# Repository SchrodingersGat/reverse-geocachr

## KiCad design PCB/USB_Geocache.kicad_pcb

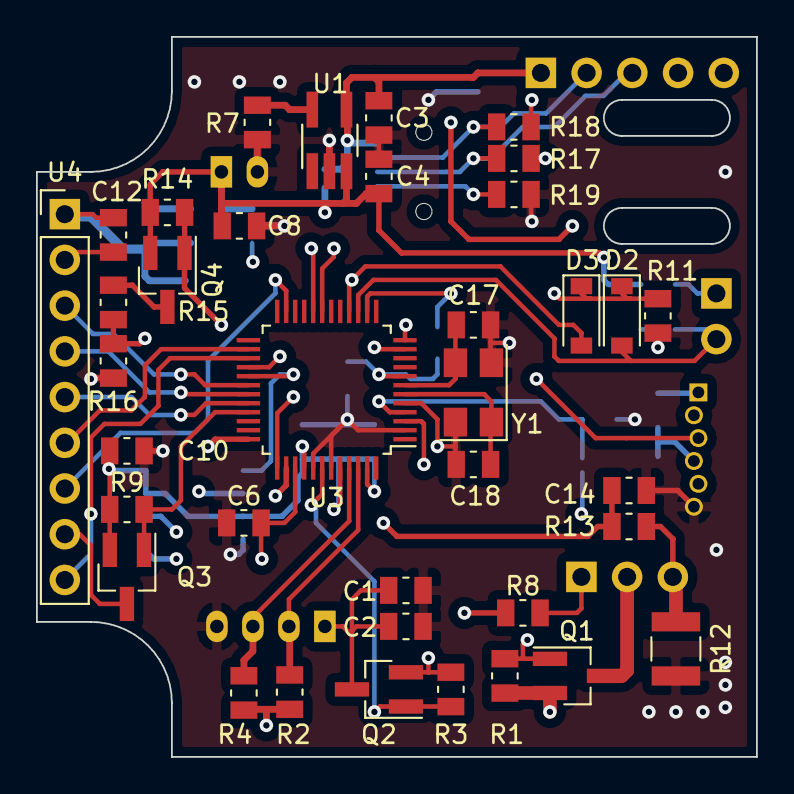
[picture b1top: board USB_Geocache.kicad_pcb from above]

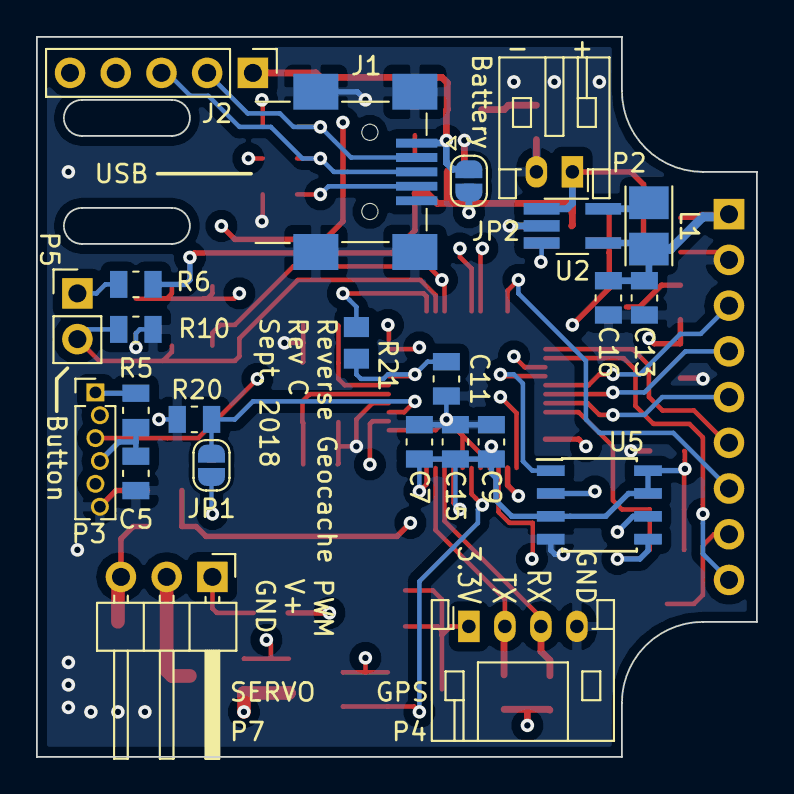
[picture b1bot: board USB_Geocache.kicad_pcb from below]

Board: 4 copper layers, 40.0 x 40.0 mm, 61 parts (24 on the bottom side), 39 nets.

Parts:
C1, C5, C7, C8, C9, C10, C11, C15, C16: 0.1uF; C_0805_2012Metric
C2, C6, C12, C13, C14: 10uF; C_0805_2012Metric
C3, C4: 4.7uF; C_0805_2012Metric
C17, C18: 18pF; C_0805_2012Metric
D2, D3: D; D_SOD-123
J1: USB_B_Mini; USB_Mini-B_Lumber_2486_Horizontal
J2: USB_ALT; PinHeader_1x05_P2.54mm_Vertical
JP1: Boot; SolderJumper-2_P1.3mm_Open_RoundedPad1.0x1.5mm
JP2: 5V; SolderJumper-2_P1.3mm_Open_RoundedPad1.0x1.5mm
L1: 10uH; L_Taiyo-Yuden_NR-24xx_HandSoldering
P2: Battery; JST_PH_S2B-PH-K_1x02_P2.00mm_Horizontal
P3: SWD; PinHeader_1x06_P1.27mm_Vertical
P4: GPS; JST_PH_S4B-PH-K_1x04_P2.00mm_Horizontal
P5: Button; PinHeader_1x02_P2.54mm_Vertical
P7: Servo; PinHeader_1x03_P2.54mm_Horizontal
Q1, Q2, Q3, Q4: DMP3099L; SOT-23_Handsoldering
R1, R3, R5, R6, R7, R8, R9, R11, R13, R14, R15: 4K7; R_0805_2012Metric
R2, R4, R10, R16, R20, R21: 10K; R_0805_2012Metric
R12: 0R1; R_1210_3225Metric
R17, R18: 0; R_0805_2012Metric
R19: 100K; R_0805_2012Metric
U1: MCP73831-2-OT; TSOT-23-5_HandSoldering
U2: LM3670MF; TSOT-23-5_HandSoldering
U3: LPC11U68JBD48E; LQFP-48_7x7mm_P0.5mm
U4: CR2013-MI2120; PinHeader_1x09_P2.54mm_Vertical
U5: 25LC640A-I/SN; SOIC-8_3.9x4.9mm_P1.27mm
Y1: 8MHz; Crystal_SMD_5032-4Pin_5.0x3.2mm

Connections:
+3V3: C7.1, C9.1, C10.2, C11.1, C12.1, C13.1, C15.1, C16.1, JP1.1, L1.1, P3.1, Q2.2, Q3.2, R2.1, R3.1, R4.1, R5.1, R8.1, R9.1, R21.1, U2.4, U3.8, U3.40, U3.44, U3.47, U4.1, U5.3, U5.7, U5.8
+5V: C3.1, J1.1, J2.1, JP2.1, U1.4
+BATT: C4.1, C8.1, JP2.2, P2.1, Q1.2, Q4.2, R1.2, R6.1, R14.1, U1.3, U2.1
/BUTTON: D2.2, P5.2, R10.1, U3.15
/CS_EEPROM: U3.29, U5.1
/EN: D2.1, D3.1, R11.1, U2.3
/GPS_PWR: Q2.1, R3.2, U3.42
/GPS_RX: P4.3, R4.2, U3.45
/GPS_TX: P4.2, R2.2, U3.46
/I_SERVO: C14.1, R13.1, U3.38
/LDC_BL: Q3.1, R9.2, U3.33
/OSC1: C18.1, U3.6, Y1.1
/OSC2: C17.1, U3.7, Y1.3
/SERVO_EN: Q1.1, R1.1, U3.11
/SERVO_PWM: P7.1, R8.2, U3.12
/SPI_MISO: U3.27, U4.9, U5.2
/SPI_MOSI: U3.26, U4.6, U5.5
/SPI_SCK: U3.23, U4.7, U5.6
/SWCLK: P3.3, U3.28
/SWDIO: P3.2, U3.37
/SW_ENABLE: D3.2, U3.16
/SW_RESET: C5.1, P3.4, R5.2, U3.3
/USB_D+: R17.1, U3.20
/USB_D-: R18.1, U3.19
/VMEAS_CTRL: Q4.1, R14.2, U3.36
/V_BATT: C6.1, R15.2, R16.1, U3.39
GND: C1.2, C2.2, C3.2, C4.2, C5.2, C6.2, C7.2, C8.2, C9.2, C10.1, C11.2, C12.2, C13.2, C14.2, C15.2, C16.2, C17.2, C18.2, J1.5, J1.6, J2.5, P2.2, P3.6, P4.4, R7.2, R10.2, R11.2, R12.2, R16.2, R19.2, R20.2, U1.2, U2.2, U3.2, U3.5, U3.41, U3.43, U4.2, U5.4, Y1.2, Y1.4
unnamed: C1.1, C2.1, P4.1, Q2.3
unnamed: J1.2, J2.2, R18.2
unnamed: J1.3, J2.3, R17.2
unnamed: J1.4, J2.4, R19.1
unnamed: JP1.2, R20.1, U3.4
unnamed: L1.2, U2.5
unnamed: P5.1, R6.2
unnamed: P7.2, Q1.3
unnamed: P7.3, R12.1, R13.2
unnamed: Q4.3, R15.1
unnamed: R7.1, U1.5
unnamed: R21.2, U3.14

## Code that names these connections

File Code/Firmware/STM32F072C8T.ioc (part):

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Mcu.Name=STM32F072C(8-B)Tx
Mcu.Package=LQFP48
Mcu.UserName=STM32F072C8Tx
PA0.GPIOParameters=GPIO_Label
PA0.GPIO_Label=V_BAT
PA0.Mode=IN0
PA0.Signal=ADC_IN0
PA1.GPIOParameters=GPIO_Label
PA1.GPIO_Label=I_SERVO
PA1.Mode=IN1
PA1.Signal=ADC_IN1
PA11.Mode=Device
PA11.Signal=USB_DM
PA12.Mode=Device
PA12.Signal=USB_DP
PA13.Mode=Serial_Wire
PA13.Signal=SYS_SWDIO
PA14.Mode=Serial_Wire
PA14.Signal=SYS_SWCLK
PA2.GPIOParameters=GPIO_Label
PA2.GPIO_Label=GPS_TX
PA2.Mode=Asynchronous
PA2.Signal=USART2_TX
PA3.GPIOParameters=GPIO_Label
PA3.GPIO_Label=GPS_RX
PA3.Mode=Asynchronous
PA3.Signal=USART2_RX
PA4.GPIOParameters=GPIO_Label
PA4.GPIO_Label=GPS_PWR
PA4.Signal=GPIO_Output
PA5.Mode=Full_Duplex_Master
PA5.Signal=SPI1_SCK
PA6.Mode=Full_Duplex_Master
PA6.Signal=SPI1_MISO
PA7.Mode=Full_Duplex_Master
PA7.Signal=SPI1_MOSI
PA8.GPIOParameters=GPIO_Label
PA8.GPIO_Label=SERVO_PWM
PA8.Signal=GPIO_Output
PA9.GPIOParameters=GPIO_Label
PA9.GPIO_Label=SERVO_PWR
PA9.Signal=GPIO_Output
PB0.GPIOParameters=GPIO_Label
PB0.GPIO_Label=LCD_CS
PB0.Signal=GPIO_Output
PB1.GPIOParameters=GPIO_Label
PB1.GPIO_Label=LCD_DC
PB1.Signal=GPIO_Output
PB10.GPIOParameters=GPIO_Label
PB10.GPIO_Label=LCD_RESET
PB10.Signal=GPIO_Output
PB2.GPIOParameters=GPIO_Label
PB2.GPIO_Label=LCD_BL
PB2.Signal=GPIO_Output
PB5.GPIOParameters=GPIO_Label
PB5.GPIO_Label=CS_EEPROM
PB5.Signal=GPIO_Output
PB8.GPIOParameters=GPIO_Label
PB8.GPIO_Label=BUTTON
PB8.Signal=GPIO_Input
PB9.GPIOParameters=GPIO_Label
PB9.GPIO_Label=SW_ENABLE
PB9.Signal=GPIO_Output
RCC.SYSCLKFreq_VALUE=36000000
RCC.SYSCLKSource=RCC_SYSCLKSOURCE_PLLCLK

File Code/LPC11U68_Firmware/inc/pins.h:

#ifndef INC_PINS_H_
#define INC_PINS_H_

#include <stdint.h>
#include <stdbool.h>

#include "board.h"

/* GPIO Pins (General)
 * SW_ENABLE = P0.5
 * BUTTON = P0.4
 * SERVO_PWM = P2.2 (STC0_OUT1)
 * SERVO_EN = P0.2
 * GPS_PWR = P0.17
 */

#define ENABLE_PORT 1
#define ENABLE_PIN 20

#define BUTTON_PORT 0
#define BUTTON_PIN 4

#define SERVO_PWM_PORT 2
#define SERVO_PWM_PIN 2

#define SERVO_EN_PORT 0
#define SERVO_EN_PIN 2

#define GPS_PWR_PORT 0
#define GPS_PWR_PIN 17

/* LCD GPIO Pins as follows:
 * CS = P0.11		- Chip Select
 * DC = P0.12		- Data / Command
 * RESET = P0.13	- Reset
 * BL = P0.14		- Backlight enable
 */

#define LCD_CS_PORT 0
#define LCD_CS_PIN 11

#define LCD_DC_PORT 0
#define LCD_DC_PIN 13

#define LCD_RST_PORT 0
#define LCD_RST_PIN 12

#define LCD_BL_PORT 0
#define LCD_BL_PIN 14

/* SPI Pins (SSP0)
 * SPI_SCK = P0.6
 * SPI_MISO = P0.8
 * SPI_MOSI = P0.9
 */

#define SPI_SCK_PORT 0
#define SPI_SCK_PIN 6

#define SPI_MISO_PORT 0
#define SPI_MISO_PIN 8

#define SPI_MOSI_PORT 0
#define SPI_MOSI_PIN 9

/* UART Pins (UART0)
 * UART_RX = P0.18
 * UART_TX = P0.19
 */

#define UART_RX_PORT 0
#define UART_RX_PIN 18

#define UART_TX_PORT 0
#define UART_TX_PIN 19

void InitPins(void);

// Pin functions
void LCD_BacklightOn(bool on);
void GPS_PowerOn(bool on);
void Servo_PowerOn(bool on);

#endif /* INC_PINS_H_ */

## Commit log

2016-01-19 Added first common files
2016-01-27 Additions to the "common" directory - The firmware compiles properly with these files
2016-01-27 v1.0 firmware (compiles, displays stuff on screen)
2016-01-27 Moved the LCD font files to the "common" directory
2016-01-27 Rearranged directory structure Changes to .gitignore
2016-01-28 Added extern "C" around common methods so they work in Qt also
2016-01-28 First commit of GUI Some functions aren't working ATM but it is compiling and running OK
2016-01-28 Added waypoint distance calculation Fixes to a lot of GUI features (getting close to fully functional again)
2016-01-28 Included <math.h> for distance trig calcs
2016-01-29 Code cleanup and LCD improvements (for both the GUI and the firmware)
2016-01-29 Committed PCB files (work still to be done here)
2016-01-29 GUI - user can move clues around properly now
2016-01-29 Firmware - LCD display improvements
2016-01-29 Changed display of waypoint threshold to integer units
2016-01-29 GUI - proper indication of currently selected clue in google-map window
2016-01-29 GUI - fixed a javascript bug, map now properly centers on selected clue
2016-01-29 GUI - user can now delete clues from anywhere in the list
2016-01-30 Box responds to HID messages properly now
2016-01-30 Correctly reading the box info and can skip back/forward clues
2016-01-30 GUI - can now request clue text data!
2016-01-30 Waypoint data messages now working properly
2016-01-30 GUI can now write clue text to the device
2016-01-30 Waypoint info (position, threshold, options, etc) now works Tx and Rx
2016-01-30 GUI - can now successfully upload all clues from box
2016-01-30 Successfully upload/download all clues OK
2016-01-30 Clue text centering now working properly
2016-01-30 Display number of clues programmed into the box
2016-02-09 Initial PCB layout
2016-02-09 Fixes to schematic
2016-02-09 Added status bits and more USB messages
2016-02-11 Released revision B of PCB
2016-03-08 Fixes to PCB
2016-03-29 Fixes to schematic and PCB layout
2016-04-02 Added current sense for the servo Added LED backlight FET for the LCD PCB improvements
2016-04-02 Silkscreen improvements
2016-04-03 Rewrote interface protocol using ProtoGen utility
2016-04-03 Fixed firmware to work with protogen packet structure
2016-04-03 Added "MSG_" prefix to USB messages
2016-04-03 Fixed common code
2016-04-03 Fixed GUI so that it works with new protogen packets
2016-04-03 Fixes to glue packets
2016-04-05 added code for reading/writing clues to external eeprom
2016-04-05 Changed resistor value
2016-06-11 First project for the new chip (LPC11U24)
2016-06-11 Got relative includes working
2016-06-11 Added all includes
2016-06-11 Got USB working
2016-06-11 Systick timer working Backlight ON/OFF working PauseMs working
2016-06-11 Added reinvoke code (don't work!)
2016-06-11 Added reset packet
2016-06-11 Added bootload command to UI Added button to clear all clue text
2016-06-20 Commented out reenter-isp code (works, kinda. weird error)
2016-06-28 Still can't figure out the SPI errors...
2016-09-29 SPI is now working
2016-09-29 gitignore Firmware_Old directory
2016-09-29 Buffering color data seems to increase speed slightly
2016-11-07 Text rendering is working again
2017-05-03 Added LCD submodule
2017-05-03 Rearranging firmware
    ( New STM32 code )
2017-05-03 PCB updates
2017-05-03 Updated .gitignore
2017-05-03 Initial commit for display code
2017-05-03 Project file fixes
2017-05-04 Improved display routine
    - Initial coding for state machine
2017-07-22 Removed old LPC firmware
2017-07-22 Removed old PIC firmware
2017-07-23 Regenerated protocol
2017-07-23 Removed old GUI code
2017-07-23 Added new GUI code
2017-07-23 Updated display constants
2017-07-23 Added settings structure to protocol
2017-07-23 UI tweaks
2017-07-23 Updated LCD text routine
    Character rendering is now much faster
2017-07-23 Added lat-lon helper script
2017-07-23 UART rx is working
    Skeleton for GPS parsing
2018-03-01 Updated protocol and UI improvements
2018-03-04 Updated schematics for STM32F072
    * No crystal required for USB
    * Higher SPI speed (18MHz)
    * Simplified some circuits
    * Fixed current draw issues (e.g. for Vmeas resistor divider)
2018-03-09 Added Load/Save functionality for clue files
    - Implemented using QSettings structure
2018-03-10 UART GPS decoding now working
    This took some work to understand:
    a) Converting DDMM.MMMM format to decimal degrees
    b) Enable floating point support for sscanf with linker flag "-u scanf_float"
2018-03-10 Fixed math linker issue
    - Unlink "c math" library to enable sqrt to work
2018-03-10 Work on box state machine
    The state machine determines what is displayed on the LCD,
    based on the GPS data / state of clues / etc
2018-03-11 Added reception indicator and improved state machine
    - Added bar display to top-left corner
    - Improved state machine logic with SetState function
    - Added state timer
2018-03-11 Implemented function to calculate waypoint heading
    https://stackoverflow.com/questions/3932502/calculate-angle-between-two-latitude-longitude-points
2018-03-11 Implemented more clue types
    SHOW_HEADING - display heading to target in degrees
    SHOW_CARDINAL - display heading in e.g. NW / SE / W
2018-03-11 Improve GPS error reporting
2018-03-19 PCB Layout
    - Completed PCB layout for new processor (Rev C)
2018-03-19 Further PCB tweaks
2018-06-17 Using the STM32F072 discovery board
2018-06-17 Deallocated unused pins
2018-06-17 Fixed SPI parameters
2018-06-18 Added skeleton for LPC firmware
    - Yep, going back to the LPC
    - USB HID is MUCH simpler to use!
    - Faster SPI (up to 25Mbit on some units)
    - Internal EEPROM (enough to store box state)
    - Waypoints can be written to FLASH
2018-06-18 SysTick and PauseMs now working
2018-06-18 Added mapview.html
    OMG how did this get deleted :'( GIT NOOO
2018-06-19 Once again communicating with PC GUI via USB
    - Sends box status packet upon request
2018-06-19 Skeleton for USB message decoding
2018-06-19 Store settings data in EEPROM
    - Settings are double-buffered and use protogen packet structure
    - Preserves compatibility as much as possible
    - Settings checksum is calculated
    - If checksum does not match, configure 'default' settings and write back to EEPROM
2018-06-22 Some further updates
2018-06-25 Add ability to read clues from flash memory
    - Assigned 0x3C000-0x40000 to store waypoint data
    - No functionality (yet) to write to flash
    - Protogen now handles encoding of entire Clue_t structure
2018-06-25 Update UI to match new firmware and protocol changes
2018-07-31 More work on FLASH programming
    - Read clues from FLASH
    - Erase FLASH and write entire set of clues
2018-08-09 Added checksum to clue info pcaket
2018-08-09 Firmware updates
2018-08-09 Fixes for GUI comms
    - Mutex lock a bunch of stuff
    - Ability to write box settings
2018-08-09 Add packet to write box settings
2018-08-11 Major UI code improvements
    - Mutex locked transmit() and receive() functions now control everything
    - Code much simpler
    - Comms routines are much quicker and more stable
    - Bug fixes too
    - Better code debugging
2018-08-11 Bug fixes for USB decoding on LPC side
    - Decode request packets second (due to zero-length packet requirement)
    - Bug fix for a packet decodea
2018-08-14 Small comment fixes
2018-08-14 Added upper and lower limits to waypoint threshold distance
2018-08-14 Clues now correctly written to FLASH memory
2018-08-14 Workaround for protogen bug
2018-08-14 seems to have fixed the hard-fault on FLASH write
    - NOTE TO ALL - LPC SUCKS SO MUCH
2018-08-14 Commonized waypoint calculation
2018-08-15 Better checksum management
    - Checksum of each clue checked on upload / download
    - Memset Clue_t to zero first
2018-08-15 Fix welcome message loading
2018-08-20 Regenerating project for the LPC11U68
    - Hopefully works better :'(
2018-08-20 Configure PID and VID
2018-08-20 SysTick timer now works
2018-08-20 EEPROM read / write now working a treat
2018-08-21 Looking to get SPI working
2018-08-21 Moving towards operational SPI
    - Pin mux is the worst
    - Seriously
2018-08-26 LCD now working!
    - The RESET pin was not working properly
    - Wait for SPI transactions to clear when CS pin goes low
    - SPI running at 8MHz (bottleneck is currently the delay between SPI transactions)
2018-08-26 Enable 16-bit SPI transactions for color data
    - Significant increase in refresh speed
2018-08-27 Skeleton code for GPS / UART
2018-08-27 GPS reception working fine!
    - Changed project settings to enable floating point scanf and printf
2018-08-28 Display code working (mostly)
    - GPS fixes when PFI = 1 (if HDoP < 2.5)
2018-08-28 Further fixes to firmware:
    - Updated flash memory addressing for new chip (flash writes now work)
    - Fix GPS calculations (include math lib)
2018-08-28 Fix screen flickering
2018-10-09 PCB / BOM stuff
2018-11-08 Update pinout for the new PCB
    - NOTE - The MOSI and MISO pins were flipped :'(
2018-11-08 Fixed some pin errors
    - LCD_DC and LCD_RST pins were flipped (however both GPIO so OK to just switch in firmware)
    - P0.11 to P0.14 are not 'GPIO' in the default mode (fixed this)
    - SPI_CLK pin is actually FUNC_2 not FUNC_1
    - Enable .bin file generation
2018-11-11 Stupid LPC datasheet
    - PIO0_5 is open-drain only (buried deep in the datasheet)
    - Enable output moved to PIO1_21
    - Proper functions for turning backlight / servo / gps ON/OFF
2018-11-12 Added power-down message when long-pressing button
